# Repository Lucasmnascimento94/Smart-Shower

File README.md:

# Smart-Shower

This is an extended version of the project I made for my computer arquitecture class. 

# Goal
The Smart-Shower aims to provide a more efficient, personalized, and intelligent way to manage the shower experience. In many homes—mine included—it can take several minutes for water to reach a comfortable temperature due to the delay in hot water arriving through the pipes. Manually adjusting the valve each time is tedius and this system introduces a smart interface to control the shower valve (or other applicable valves) with a focus on user comfort, energy efficiency, and system safety.

# Features
-> Personalized Temperature Presets: Each user can save their preferred shower temperature settings for one-touch access.

-> Remote Start Functionality: Users can activate the shower remotely, allowing the water to reach the desired temperature before they step in—eliminating wait time.

-> Hot Water Monitoring: Tracks the decline of hot water temperature and alerts the user when they are about to run out—especially useful for homes that use hot water tanks.

-> Usage Tracking: Monitors water and energy usage per session. Data is logged and associated with individual users for long-term insights and potential conservation.

-> Cold Temperature Alert: Sends a warning if pipe temperatures drop too low, helping to prevent frozen or burst pipes—especially relevant for homes in colder northern climates (like mine).

# Planned Future Enhancements

-> Rich Media User Interface: Build an advanced touchscreen UI that supports media platforms such as Spotify and YouTube for a more immersive shower experience.

-> Metal Contamination Detection: Integrate a sensor to detect the presence of metals in the water—an issue that affects my home’s plumbing.

-> Smart Safety Alarms and Automation: Extend system logic to trigger alarms and automated valve actions based on detected anomalies in temperature or water quality.

The first version was made using an ATMEGA 168A, coded in assembly and all the assembled componnets were placed with loose wires in some protoboards. 

# Note
-> Because this application utilizes threads, I started to move away from the HAL functions. At first, when I started migrating from one thread to another multithreaded environment, I started adapting my working functions within certain threads. However, it was later on determined that the HAL function are not thread safe, and the programming was breaking randomly when trying to run some HAL functions. To solve this issue, I started to manipulate the register in a low level manner. Trying to avoid reinventing the wheel, I started reading the STM documentation and controlling the registers using the variable names in the RM and the macros that are provided in the STM header files. With this approach it was possible to create mutaxes and make sure that no race condition is preventing my code from running.

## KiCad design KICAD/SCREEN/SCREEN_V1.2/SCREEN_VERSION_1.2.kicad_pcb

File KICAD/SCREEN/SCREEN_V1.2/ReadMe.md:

## Update Overview - Power Distribution
  In this version, a critical flaw in the power distribution design has been corrected. Previously, the STM32F469IIT6 microcontroller was powered by an ASM1117-3.3 voltage regulator, stepping down from a 12V input. However, the resulting power dissipation caused the regulator to overheat, leading to unstable MCU behavior. The issue became more pronounced after introducing multi-threading in the firmware, which increased the system's current draw. At that point, the ASM1117 began to overheat severely, risking unpredictable system failures and potential board damage.

  This overheat was detected in a prior version where devices were powered by the same regulator. In an attempt to solve this issue and still use the same regulator (Because I have many in stock), I've added dedicated regulators for some devices and it worked at a certain degree. However, it was yet not possible to place the external flash memory without overheating the ASM that powers the STM32F469. Then this update aims to fix this flaw in order to be able to utilize all the intended devices and maintain the program reliability.  

## Update Overview - Touch Screen Controller
This version removes the XPT20 touchscreen controller from the design. In version 1.0 (not publicly released), issues with the touchscreen were caused by incorrect circuitry and the absence of a controller to compensate for it. The XPT20 was originally added as a workaround to assist with potential problems in reading ADC values directly—such as noise, hardware design flaws, or programming errors. However, in version 1.1, I successfully read the touchscreen using the STM32F469’s internal ADCs without needing the XPT20. As a result, this external controller has been removed in this version to simplify the design.

Version 1.1 also introduced multi-threading, with one dedicated thread continuously reading the X-axis ADC values. Based on these readings, the system calls the scan_ function, which samples multiple values to compute both X and Y coordinates. This function dynamically reconfigures the GPIOs to alternate between driving and reading different touchscreen lines. However, this dynamic GPIO switching proved problematic in a multithreaded environment. In this update, I'm testing a workaround by adding minimal extra circuitry and using an ADC multiplexer to eliminate the need for constant GPIO reconfiguration. The goal is to reduce the processing overhead and improve stability under concurrent execution.

## Update

| Removed Component |  New Component     | Datasheet|
| ---------------:  | ---------------:   | ---------|
|AMS1117-3.3 |LM2576T-ADJ/NOPB  | https://www.ti.com/general/docs/suppproductinfo.tsp?distId=10&gotoUrl=https%3A%2F%2Fwww.ti.com%2Flit%2Fgpn%2Flm2576hv|
| XPT20 | N/A | https://www.alldatasheet.com/html-pdf/1649104/ETC2/XPT2046/111/1/XPT2046.html |

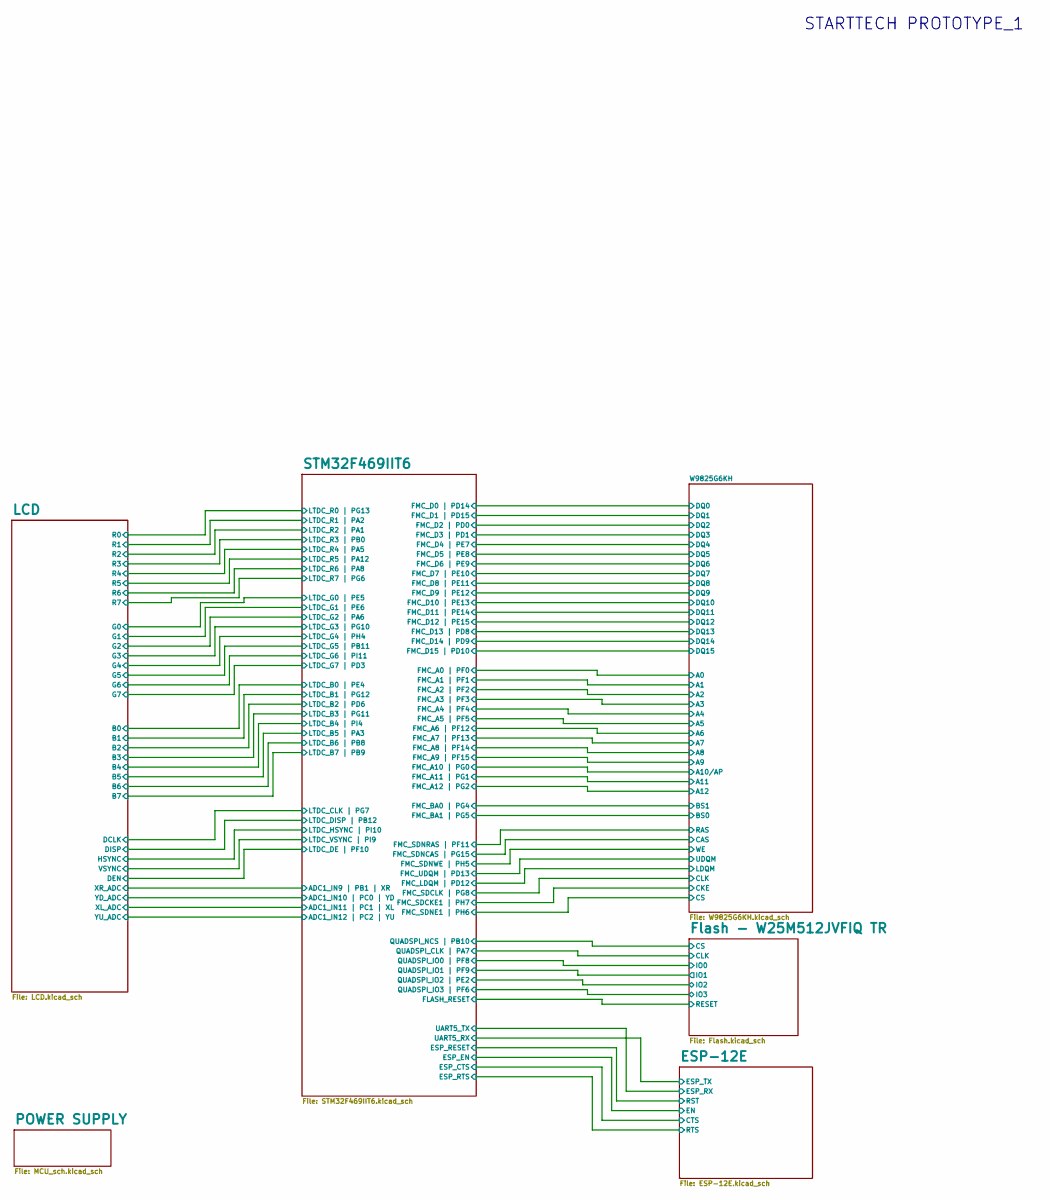
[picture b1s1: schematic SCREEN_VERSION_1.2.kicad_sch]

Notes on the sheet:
STARTTECH PROTOTYPE_1

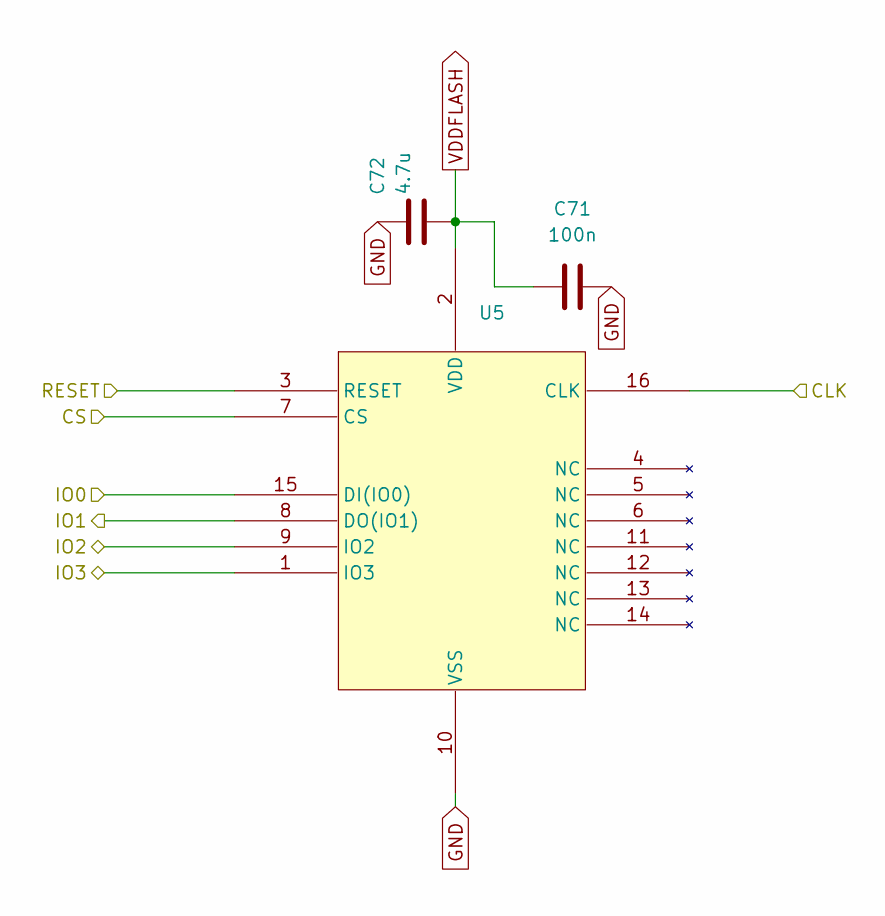
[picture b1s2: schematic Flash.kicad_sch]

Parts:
C71: 100n; C_0402_1005Metric
C72: 4.7u; C_0603_1608Metric
U5: W25M512JVFIQ

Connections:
/Flash - W25M512JVFIQ TR/CLK: U5.16 (CLK); also elsewhere on the board
/Flash - W25M512JVFIQ TR/CS: U5.7 (CS); also elsewhere on the board
/Flash - W25M512JVFIQ TR/IO0: U5.15 (DI(IO0)); also elsewhere on the board
/Flash - W25M512JVFIQ TR/IO1: U5.8 (DO(IO1)); also elsewhere on the board
/Flash - W25M512JVFIQ TR/IO2: U5.9 (IO2); also elsewhere on the board
/Flash - W25M512JVFIQ TR/IO3: U5.1 (IO3); also elsewhere on the board
/Flash - W25M512JVFIQ TR/RESET: U5.3 (RESET); also elsewhere on the board
GND: C71.2, C72.1, U5.10 (VSS); also elsewhere on the board
VDDFLASH: C71.1, C72.2, U5.2 (VDD); also elsewhere on the board

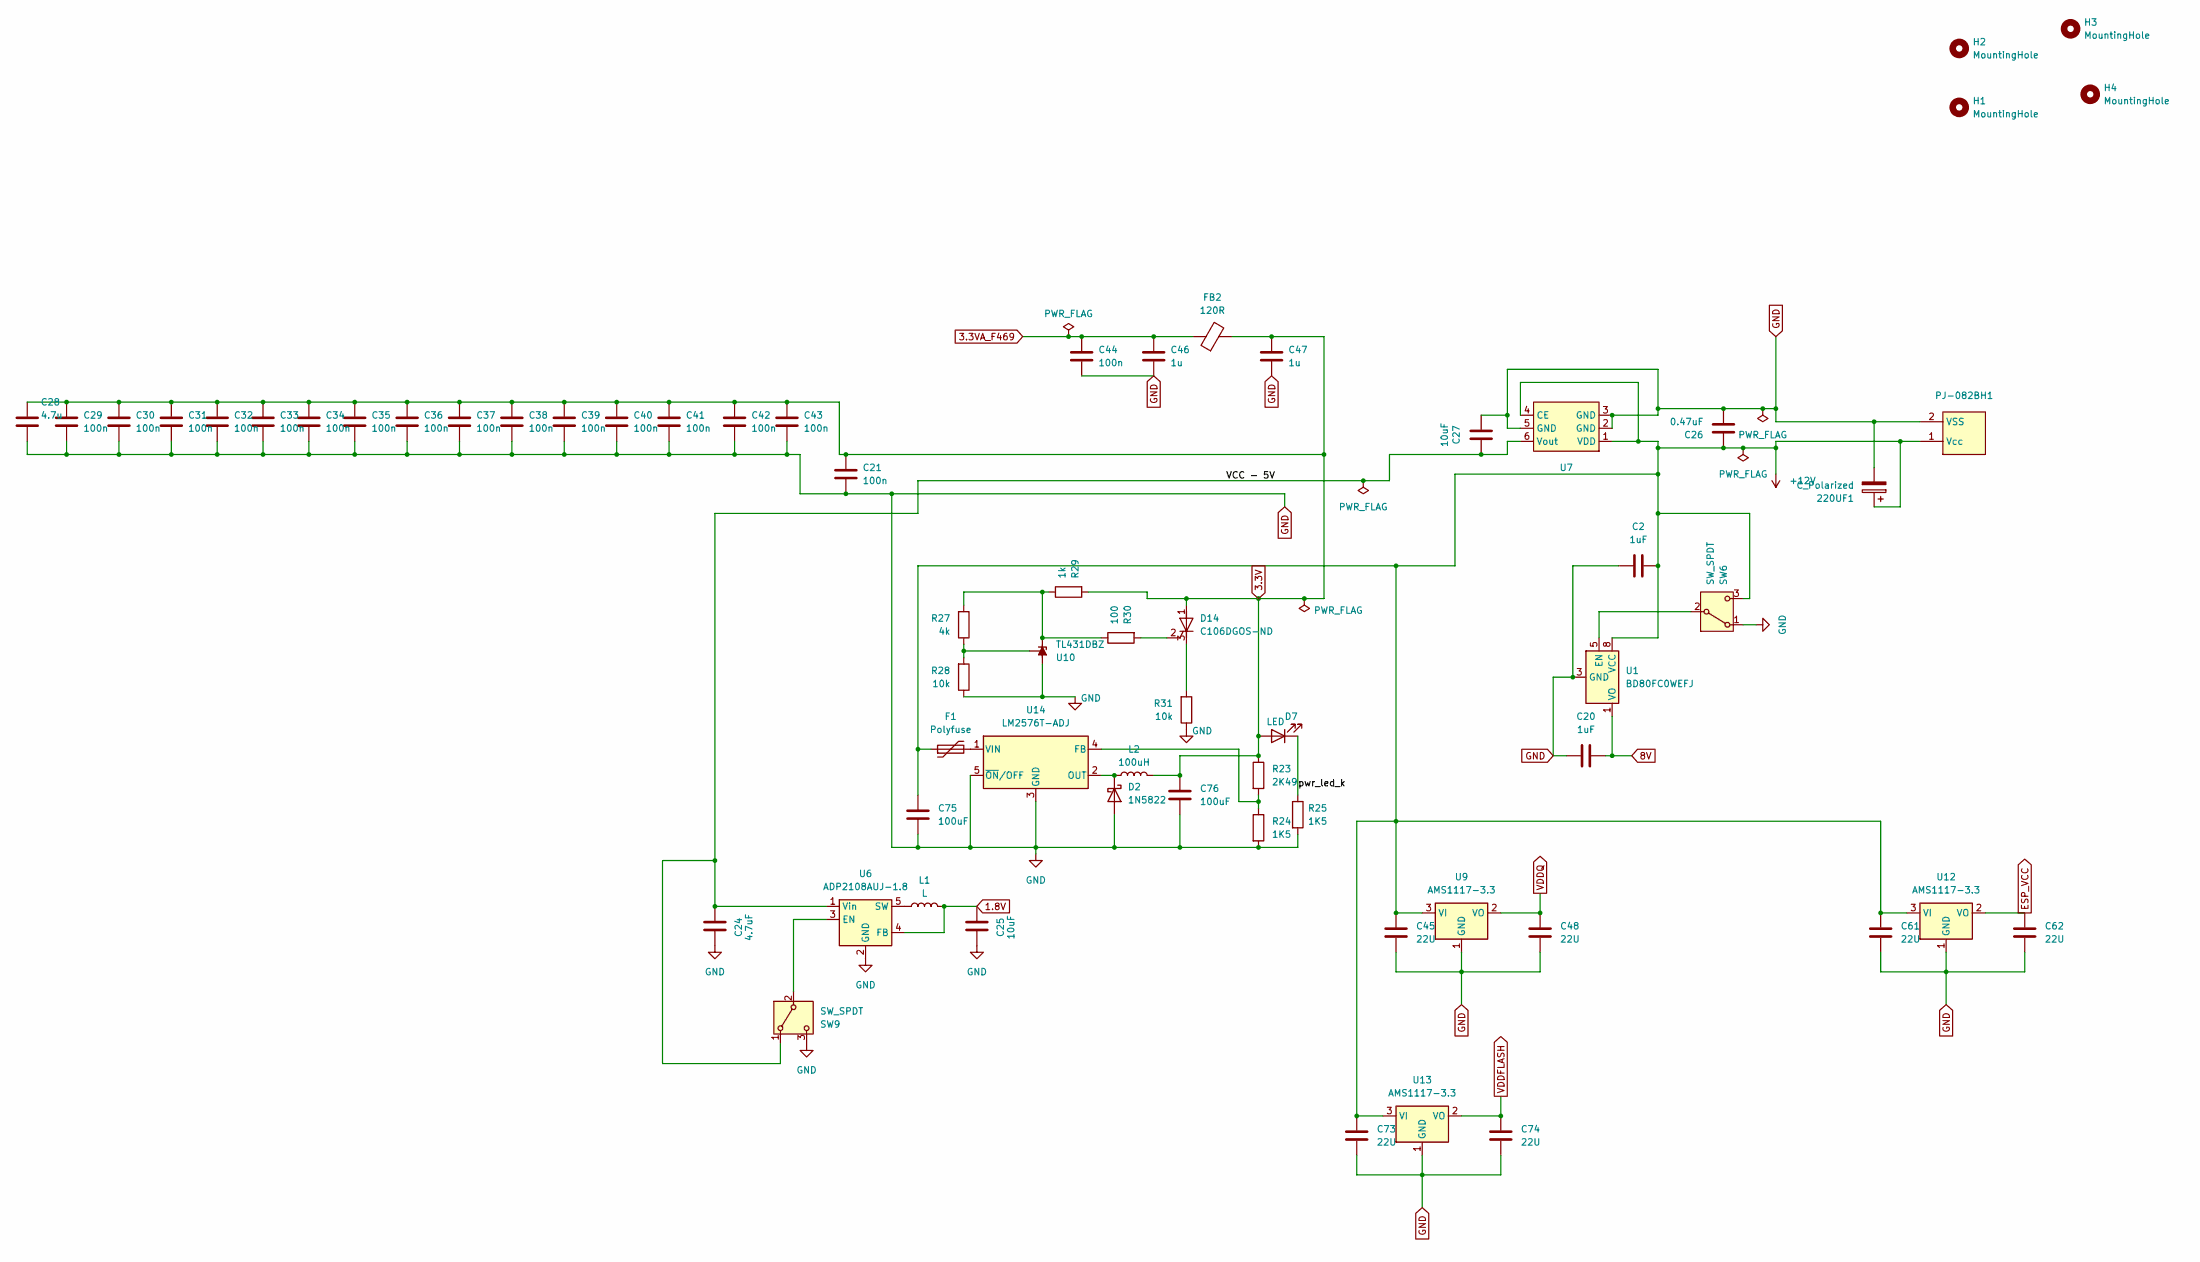
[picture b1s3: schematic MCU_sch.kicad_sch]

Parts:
220UF1: C_Polarized; C_Disc_D3.0mm_W1.6mm_P2.50mm
C2, C20: 1uF; C_0603_1608Metric
C21, C29, C30, C31, C32, C33, C34, C35, C36, C37, C38, C39, C40, C41, C42, C43, C44: 100n; C_0402_1005Metric
C24: 4.7uF; C_0603_1608Metric
C25, C27: 10uF; C_0805_2012Metric
C26: 0.47uF; C_0603_1608Metric
C28: 4.7u; C_0603_1608Metric
C45, C48, C61, C62, C73, C74: 22U; C_0805_2012Metric
C46, C47: 1u; C_0603_1608Metric
C75, C76: 100uF; C_1210_3225Metric_Pad1.33x2.70mm_HandSolder
D2: 1N5822; D_DO-201AD_P15.24mm_Horizontal
D7: LED; LED_0603_1608Metric
D14: C106DGOS-ND; SIP3_11.6x8.5mm
F1: Polyfuse; Fuse_1206_3216Metric
FB2: 120R; L_0603_1608Metric
H1, H2, H3, H4: MountingHole; MountingHole_3.2mm_M3
L1: L; L_0603_1608Metric_Pad1.05x0.95mm_HandSolder
L2: 100uH; SRN8040-101M
PJ-082BH1: BarrelJack_CUI_PJ-063AH_Horizontal
R23: 2K49; R_0402_1005Metric
R24, R25: 1K5; R_0402_1005Metric
R27: 4k; R_0402_1005Metric
R28, R31: 10k; R_0402_1005Metric
R29: 1k; R_0402_1005Metric
R30: 100; R_0402_1005Metric
SW6, SW9: SW_SPDT; SW_Slide_SPDT_Straight_CK_OS102011MS2Q
U1: BD80FC0WEFJ; HTSOP-8-1EP_3.9x4.9mm_P1.27mm_EP2.4x3.2mm
U6: ADP2108AUJ-1.8; TSOT-23-5
U7: R1501S050B-E2-FE
U9, U12, U13: AMS1117-3.3; SOT-223-3_TabPin2
U10: TL431DBZ; SOT-23
U14: LM2576T-ADJ; TO-220-5_Vertical

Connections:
1.8V: C25.1, L1.2, U6.4 (FB); also elsewhere on the board
3.3V: C21.1, C28.1, C29.1, C30.1, C31.1, C32.1, C33.1, C34.1, C35.1, C36.1, C37.1, C38.1, C39.1, C40.1, C41.1, C42.1, C43.1, C47.1, C76.1, D7.2 (A), D14.1 (A), FB2.2, L2.2, R23.1, R29.2; also elsewhere on the board
3.3VA_F469: C44.1, C46.1, FB2.1; also elsewhere on the board
8V: C20.1, U1.1 (VO); also elsewhere on the board
+12V: 220UF1.1, C2.1, C26.1, C45.1, C61.1, C73.1, C75.1, F1.1, PJ-082BH1.1 (Vcc), SW6.3 (C), U1.8 (VCC), U7.1 (VDD), U7.4 (CE), U9.3 (VI), U12.3 (VI), U13.3 (VI)
/POWER SUPPLY/VCC - 5V: C24.1, C27.2, SW9.1 (A), U6.1 (Vin), U7.6 (Vout)
/POWER SUPPLY/pwr_led_k: D7.1 (K), R25.1
ESP_VCC: C62.1, U12.2 (VO); also elsewhere on the board
GND: 220UF1.2, C2.2, C20.2, C21.2, C24.2, C25.2, C26.2, C27.1, C28.2, C29.2, C30.2, C31.2, C32.2, C33.2, C34.2, C35.2, C36.2, C37.2, C38.2, C39.2, C40.2, C41.2, C42.2, C43.2, C44.2, C45.2, C46.2, C47.2, C48.2, C61.2, C62.2, C73.2, C74.2, C75.2, C76.2, D2.2 (A), PJ-082BH1.2 (VSS), R24.2, R25.2, R28.1, R31.1, SW6.1 (A), SW9.3 (C), U1.3 (GND), U1.9 (GND), U6.2 (GND), U7.2 (GND), U7.3 (GND), U7.5 (GND), U9.1 (GND), U10.3 (A), U12.1 (GND), U13.1 (GND), U14.3 (GND), U14.5 (~ON/OFF); also elsewhere on the board
unnamed: D2.1 (K), L2.1, U14.2 (OUT)
unnamed: D14.2 (G), R30.2
unnamed: D14.3 (K), R31.2
unnamed: SW6.2 (B), U1.5 (EN)
unnamed: SW9.2 (B), U6.3 (EN)
unnamed: L1.1, U6.5 (SW)
unnamed: R27.2, R29.1, R30.1, U10.1 (K)
unnamed: R27.1, R28.2, U10.2 (REF)
unnamed: R23.2, R24.1, U14.4 (FB)
unnamed: F1.2, U14.1 (VIN)
VDDFLASH: C74.1, U13.2 (VO); also elsewhere on the board
VDDQ: C48.1, U9.2 (VO); also elsewhere on the board

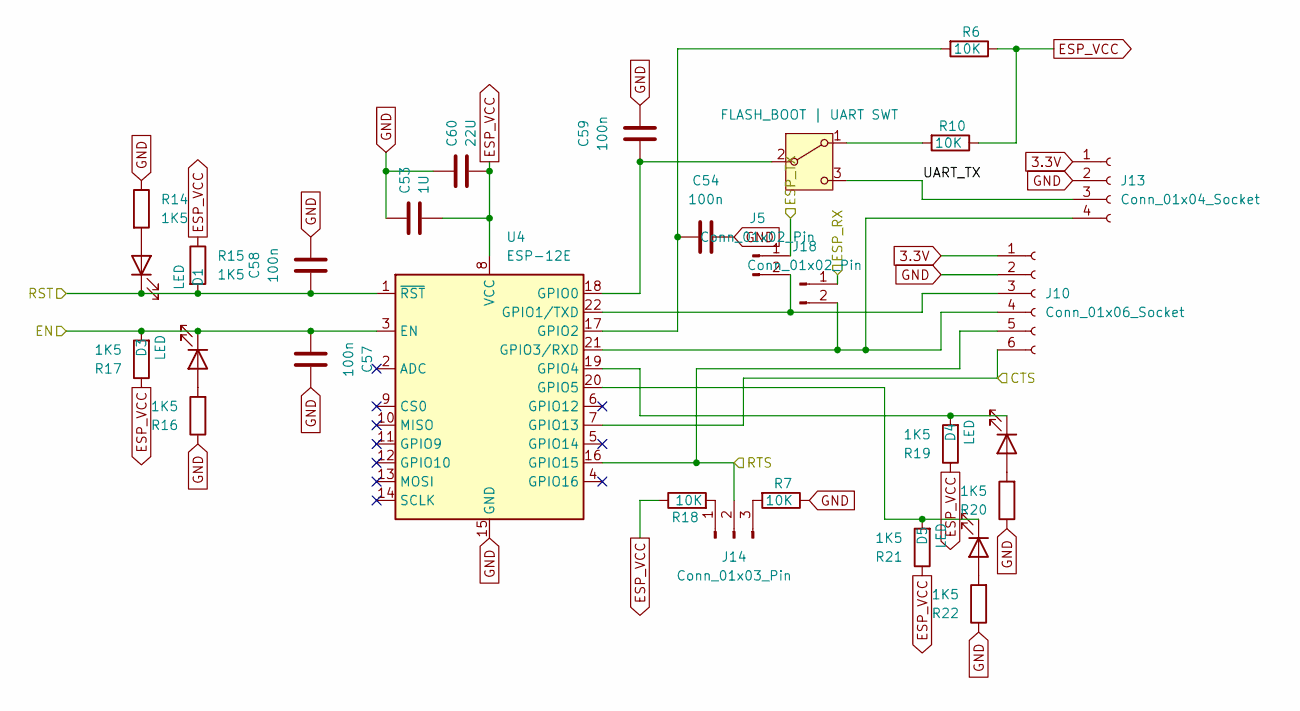
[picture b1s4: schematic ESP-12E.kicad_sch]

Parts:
C53: 1U; C_0805_2012Metric
C54, C57, C58, C59: 100n; C_0402_1005Metric
C60: 22U; C_0805_2012Metric
D1, D3, D4, D5: LED; LED_0603_1608Metric
J5, J18: Conn_01x02_Pin; PinSocket_1x02_P2.54mm_Vertical
J10: Conn_01x06_Socket; PinSocket_1x06_P2.54mm_Vertical
J13: Conn_01x04_Socket; PinSocket_1x04_P2.54mm_Vertical
J14: Conn_01x03_Pin; PinSocket_1x03_P2.54mm_Vertical
R6, R7, R10, R18: 10K; R_0402_1005Metric
R14, R15, R16, R17, R19, R20, R21, R22: 1K5; R_0402_1005Metric
SW5: FLASH_BOOT | UART SWT; SW_Slide_SPDT_Straight_CK_OS102011MS2Q
U4: ESP-12E

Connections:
3.3V: J10.1, J13.1; also elsewhere on the board
/ESP-12E/CTS: J10.6, U4.7 (GPIO13); also elsewhere on the board
/ESP-12E/EN: C57.1, D3.1 (K), R17.2, U4.3 (EN); also elsewhere on the board
/ESP-12E/ESP_RX: J18.1; also elsewhere on the board
/ESP-12E/ESP_TX: J5.1; also elsewhere on the board
/ESP-12E/RST: C58.1, D1.1 (K), R15.2, U4.1 (~RST); also elsewhere on the board
/ESP-12E/RTS: J10.5, J14.2, U4.16 (GPIO15); also elsewhere on the board
/ESP-12E/UART_TX: J13.3, SW5.3 (C)
ESP_VCC: C53.2, C60.2, R6.1, R10.1, R15.1, R17.1, R18.1, R19.1, R21.1, U4.8 (VCC); also elsewhere on the board
GND: C53.1, C54.2, C57.2, C58.2, C59.2, C60.1, J10.2, J13.2, R7.1, R14.1, R16.1, R20.1, R22.1, U4.15 (GND); also elsewhere on the board
unnamed: D1.2 (A), R14.2
unnamed: D3.2 (A), R16.2
unnamed: D4.2 (A), R20.2
unnamed: D4.1 (K), R19.2, U4.19 (GPIO4)
unnamed: D5.2 (A), R22.2
unnamed: D5.1 (K), R21.2, U4.20 (GPIO5)
unnamed: J5.2, J10.3, U4.22 (GPIO1/TXD)
unnamed: J10.4, J13.4, J18.2, U4.21 (GPIO3/RXD)
unnamed: J14.1, R18.2
unnamed: J14.3, R7.2
unnamed: R10.2, SW5.1 (A)
unnamed: C59.1, SW5.2 (B), U4.18 (GPIO0)
unnamed: C54.1, R6.2, U4.17 (GPIO2)

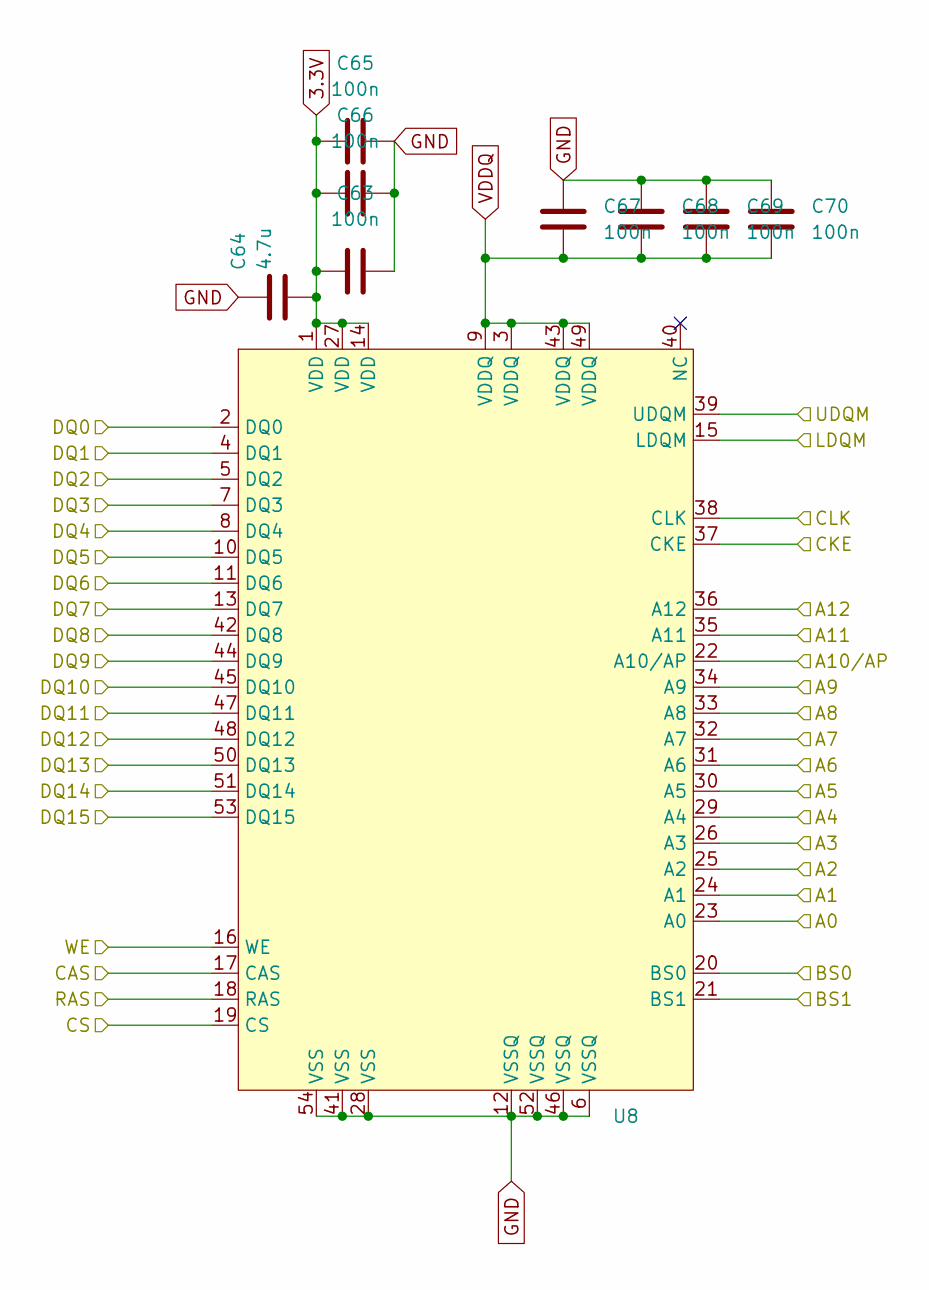
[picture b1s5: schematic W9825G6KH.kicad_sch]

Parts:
C63, C65, C66, C67, C68, C69, C70: 100n; C_0402_1005Metric
C64: 4.7u; C_0603_1608Metric
U8: W9825G6KH

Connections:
3.3V: C63.1, C64.2, C65.1, C66.1, U8.1 (VDD), U8.14 (VDD), U8.27 (VDD); also elsewhere on the board
/STM32F469IIT6/FMC_A0 | PF0: U8.23 (A0); also elsewhere on the board
/STM32F469IIT6/FMC_A1 | PF1: U8.24 (A1); also elsewhere on the board
/STM32F469IIT6/FMC_A2 | PF2: U8.25 (A2); also elsewhere on the board
/STM32F469IIT6/FMC_A3 | PF3: U8.26 (A3); also elsewhere on the board
/STM32F469IIT6/FMC_A4 | PF4: U8.29 (A4); also elsewhere on the board
/STM32F469IIT6/FMC_A5 | PF5: U8.30 (A5); also elsewhere on the board
/STM32F469IIT6/FMC_A6 | PF12: U8.31 (A6); also elsewhere on the board
/STM32F469IIT6/FMC_A7 | PF13: U8.32 (A7); also elsewhere on the board
/STM32F469IIT6/FMC_A8 | PF14: U8.33 (A8); also elsewhere on the board
/STM32F469IIT6/FMC_A9 | PF15: U8.34 (A9); also elsewhere on the board
/STM32F469IIT6/FMC_A10 | PG0: U8.22 (A10/AP); also elsewhere on the board
/STM32F469IIT6/FMC_A11 | PG1: U8.35 (A11); also elsewhere on the board
/STM32F469IIT6/FMC_A12 | PG2: U8.36 (A12); also elsewhere on the board
/STM32F469IIT6/FMC_BA0 | PG4: U8.21 (BS1); also elsewhere on the board
/STM32F469IIT6/FMC_BA1 | PG5: U8.20 (BS0); also elsewhere on the board
/STM32F469IIT6/FMC_D0 | PD14: U8.2 (DQ0); also elsewhere on the board
/STM32F469IIT6/FMC_D1 | PD15: U8.4 (DQ1); also elsewhere on the board
/STM32F469IIT6/FMC_D2 | PD0: U8.5 (DQ2); also elsewhere on the board
/STM32F469IIT6/FMC_D3 | PD1: U8.7 (DQ3); also elsewhere on the board
/STM32F469IIT6/FMC_D4 | PE7: U8.8 (DQ4); also elsewhere on the board
/STM32F469IIT6/FMC_D5 | PE8: U8.10 (DQ5); also elsewhere on the board
/STM32F469IIT6/FMC_D6 | PE9: U8.11 (DQ6); also elsewhere on the board
/STM32F469IIT6/FMC_D7 | PE10: U8.13 (DQ7); also elsewhere on the board
/STM32F469IIT6/FMC_D8 | PE11: U8.42 (DQ8); also elsewhere on the board
/STM32F469IIT6/FMC_D9 | PE12: U8.44 (DQ9); also elsewhere on the board
/STM32F469IIT6/FMC_D10 | PE13: U8.45 (DQ10); also elsewhere on the board
/STM32F469IIT6/FMC_D11 | PE14: U8.47 (DQ11); also elsewhere on the board
/STM32F469IIT6/FMC_D12 | PE15: U8.48 (DQ12); also elsewhere on the board
/STM32F469IIT6/FMC_D13 | PD8: U8.50 (DQ13); also elsewhere on the board
/STM32F469IIT6/FMC_D14 | PD9: U8.51 (DQ14); also elsewhere on the board
/STM32F469IIT6/FMC_D15 | PD10: U8.53 (DQ15); also elsewhere on the board
/STM32F469IIT6/FMC_LDQM | PD12: U8.15 (LDQM); also elsewhere on the board
/STM32F469IIT6/FMC_SDCKE1 | PH7: U8.37 (CKE); also elsewhere on the board
/STM32F469IIT6/FMC_SDCLK | PG8: U8.38 (CLK); also elsewhere on the board
/STM32F469IIT6/FMC_SDNCAS | PG15: U8.17 (CAS); also elsewhere on the board
/STM32F469IIT6/FMC_SDNE1 | PH6: U8.19 (CS); also elsewhere on the board
/STM32F469IIT6/FMC_SDNRAS | PF11: U8.18 (RAS); also elsewhere on the board
/STM32F469IIT6/FMC_SDNWE | PH5: U8.16 (WE); also elsewhere on the board
/STM32F469IIT6/FMC_UDQM | PD13: U8.39 (UDQM); also elsewhere on the board
GND: C63.2, C64.1, C65.2, C66.2, C67.2, C68.2, C69.2, C70.2, U8.6 (VSSQ), U8.12 (VSSQ), U8.28 (VSS), U8.41 (VSS), U8.46 (VSSQ), U8.52 (VSSQ), U8.54 (VSS); also elsewhere on the board
VDDQ: C67.1, C68.1, C69.1, C70.1, U8.3 (VDDQ), U8.9 (VDDQ), U8.43 (VDDQ), U8.49 (VDDQ); also elsewhere on the board
